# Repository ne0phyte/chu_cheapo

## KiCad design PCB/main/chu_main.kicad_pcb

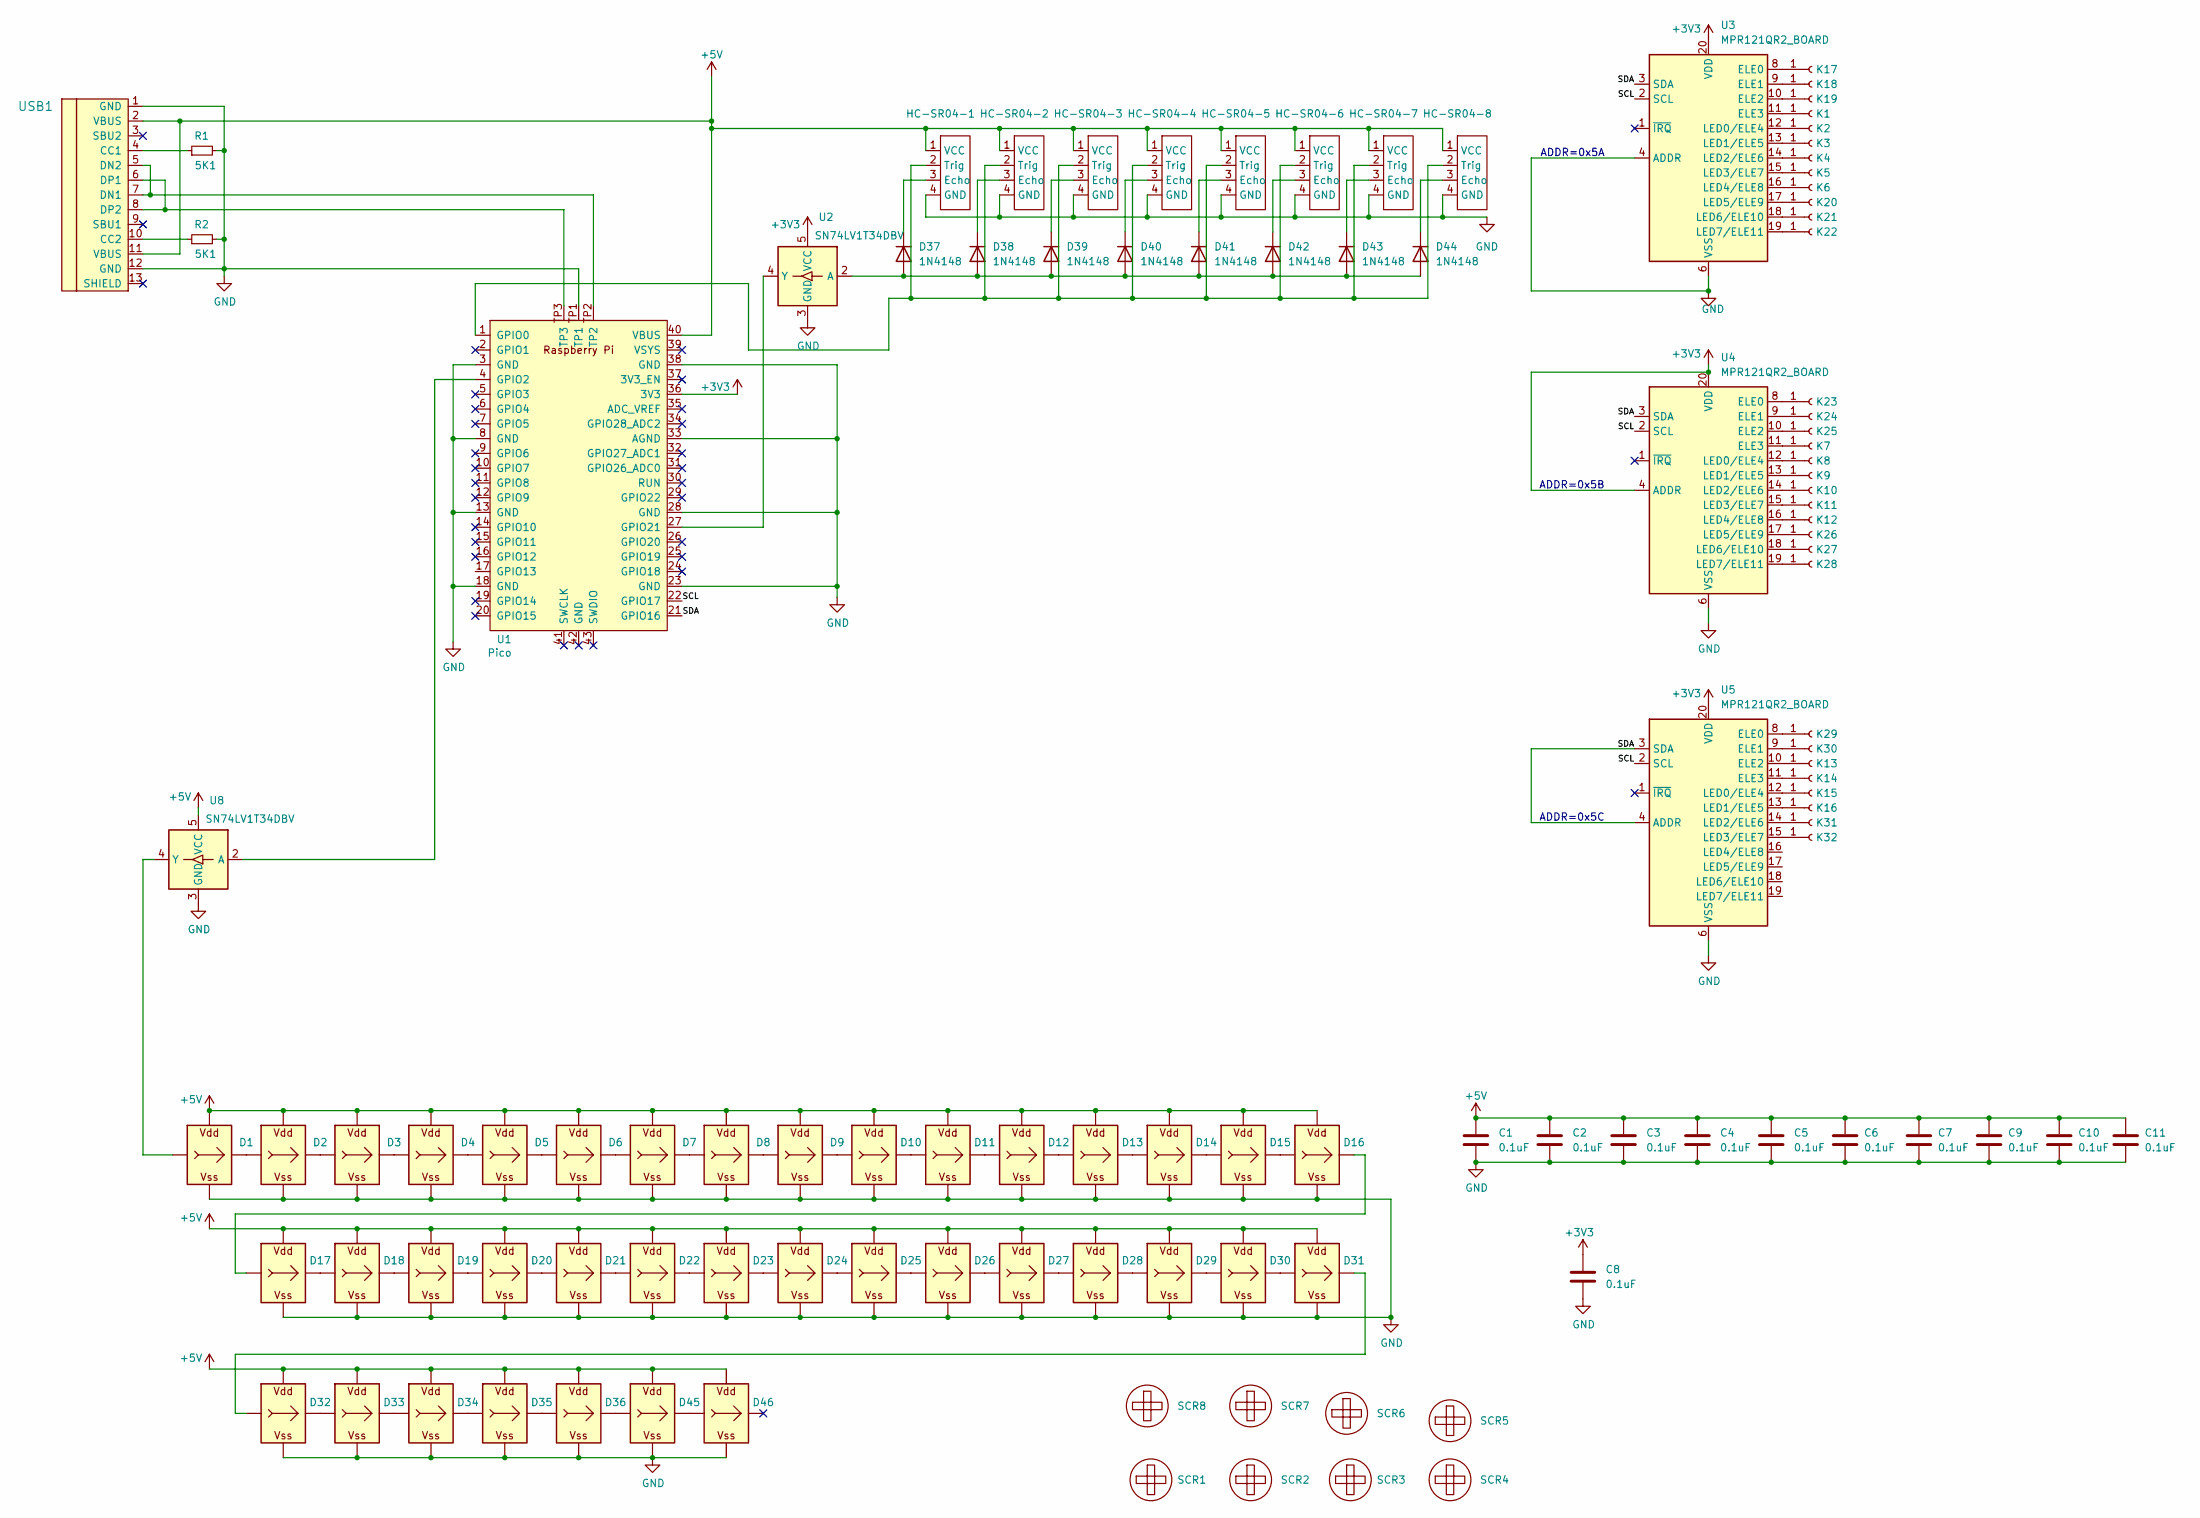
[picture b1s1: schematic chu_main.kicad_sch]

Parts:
C1, C2, C3, C4, C5, C6, C7, C8, C9, C10, C11: 0.1uF; C_0603_1608Metric_Pad1.08x0.95mm_HandSolder
D1, D2, D3, D4, D5, D6, D7, D8, D9, D10, D11, D12, D13, D14, D15, D16, D17, D18, D19, D20, D21, D22, D23, D24, D25, D26, D27, D28, D29, D30, D31, D32, D33, D34, D35, D36, D45, D46: WS2812B_Unified; WS2812D-F5
D37, D38, D39, D40, D41, D42, D43, D44: 1N4148; D_DO-35_SOD27_P7.62mm_Horizontal
HC-SR04-1, HC-SR04-2, HC-SR04-3, HC-SR04-4, HC-SR04-5, HC-SR04-6, HC-SR04-7, HC-SR04-8: HC-SR04
K1, K2, K3, K4, K5, K6, K7, K8, K9, K10, K11, K12, K13, K14, K15, K16, K17, K18, K19, K20, K21, K22, K23, K24, K25, K26, K27, K28, K29, K30, K31, K32: Conn_01x01_Female; Chu_TouchKey
R1, R2: 5K1; R_0603_1608Metric; LCSC C23186
SCR1, SCR2, SCR3, SCR4, SCR5, SCR6, SCR7, SCR8: ScrewHole; MountingHole_3.2mm_M3
U1: Pico; RPi_Pico_SMD_Pins_Strip
U2, U8: SN74LV1T34DBV; SOT-23-5_Jumper
U3, U4, U5: MPR121QR2_BOARD; MPR121_BOARD
USB1: U262-161N-4BVC11; HRO-TYPE-C-31-M-12-Assembly; LCSC C319148

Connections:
+3V3: C8.1, U1.36 (3V3), U2.5 (VCC), U3.20 (VDD), U4.4 (ADDR), U4.20 (VDD), U5.20 (VDD)
+5V: C1.1, C2.1, C3.1, C4.1, C5.1, C6.1, C7.1, C9.1, C10.1, C11.1, D1.V (VDD), D2.V (VDD), D3.V (VDD), D4.V (VDD), D5.V (VDD), D6.V (VDD), D7.V (VDD), D8.V (VDD), D9.V (VDD), D10.V (VDD), D11.V (VDD), D12.V (VDD), D13.V (VDD), D14.V (VDD), D15.V (VDD), D16.V (VDD), D17.V (VDD), D18.V (VDD), D19.V (VDD), D20.V (VDD), D21.V (VDD), D22.V (VDD), D23.V (VDD), D24.V (VDD), D25.V (VDD), D26.V (VDD), D27.V (VDD), D28.V (VDD), D29.V (VDD), D30.V (VDD), D31.V (VDD), D32.V (VDD), D33.V (VDD), D34.V (VDD), D35.V (VDD), D36.V (VDD), D45.V (VDD), D46.V (VDD), HC-SR04-1.1 (VCC), HC-SR04-2.1 (VCC), HC-SR04-3.1 (VCC), HC-SR04-4.1 (VCC), HC-SR04-5.1 (VCC), HC-SR04-6.1 (VCC), HC-SR04-7.1 (VCC), HC-SR04-8.1 (VCC), U1.40 (VBUS), U8.5 (VCC), USB1.2 (VBUS), USB1.11 (VBUS)
/SCL: U1.22 (GPIO17), U3.2 (SCL), U4.2 (SCL), U5.2 (SCL)
/SDA: U1.21 (GPIO16), U3.3 (SDA), U4.3 (SDA), U5.3 (SDA), U5.4 (ADDR)
GND: C1.2, C2.2, C3.2, C4.2, C5.2, C6.2, C7.2, C8.2, C9.2, C10.2, C11.2, D1.G (VSS), D2.G (VSS), D3.G (VSS), D4.G (VSS), D5.G (VSS), D6.G (VSS), D7.G (VSS), D8.G (VSS), D9.G (VSS), D10.G (VSS), D11.G (VSS), D12.G (VSS), D13.G (VSS), D14.G (VSS), D15.G (VSS), D16.G (VSS), D17.G (VSS), D18.G (VSS), D19.G (VSS), D20.G (VSS), D21.G (VSS), D22.G (VSS), D23.G (VSS), D24.G (VSS), D25.G (VSS), D26.G (VSS), D27.G (VSS), D28.G (VSS), D29.G (VSS), D30.G (VSS), D31.G (VSS), D32.G (VSS), D33.G (VSS), D34.G (VSS), D35.G (VSS), D36.G (VSS), D45.G (VSS), D46.G (VSS), HC-SR04-1.4 (GND), HC-SR04-2.4 (GND), HC-SR04-3.4 (GND), HC-SR04-4.4 (GND), HC-SR04-5.4 (GND), HC-SR04-6.4 (GND), HC-SR04-7.4 (GND), HC-SR04-8.4 (GND), R1.2, R2.2, U1.3 (GND), U1.8 (GND), U1.13 (GND), U1.18 (GND), U1.23 (GND), U1.28 (GND), U1.33 (AGND), U1.38 (GND), U1.TP1, U2.3 (GND), U3.4 (ADDR), U3.6 (VSS), U4.6 (VSS), U5.6 (VSS), U8.3 (GND), USB1.1 (GND), USB1.12 (GND)
unnamed: D1.I (In), U8.4 (Y)
unnamed: D1.O (Out), D2.I (In)
unnamed: D2.O (Out), D3.I (In)
unnamed: D3.O (Out), D4.I (In)
unnamed: D4.O (Out), D5.I (In)
unnamed: D5.O (Out), D6.I (In)
unnamed: D6.O (Out), D7.I (In)
unnamed: D7.O (Out), D8.I (In)
unnamed: D8.O (Out), D9.I (In)
unnamed: D9.O (Out), D10.I (In)
unnamed: D10.O (Out), D11.I (In)
unnamed: D11.O (Out), D12.I (In)
unnamed: D12.O (Out), D13.I (In)
unnamed: D13.O (Out), D14.I (In)
unnamed: D14.O (Out), D15.I (In)
unnamed: D15.O (Out), D16.I (In)
unnamed: D16.O (Out), D17.I (In)
unnamed: D17.O (Out), D18.I (In)
unnamed: D18.O (Out), D19.I (In)
unnamed: D19.O (Out), D20.I (In)
unnamed: D20.O (Out), D21.I (In)
unnamed: D21.O (Out), D22.I (In)
unnamed: D22.O (Out), D23.I (In)
unnamed: D23.O (Out), D24.I (In)
unnamed: D24.O (Out), D25.I (In)
unnamed: D25.O (Out), D26.I (In)
unnamed: D26.O (Out), D27.I (In)
unnamed: D27.O (Out), D28.I (In)
unnamed: D28.O (Out), D29.I (In)
unnamed: D29.O (Out), D30.I (In)
unnamed: D30.O (Out), D31.I (In)
unnamed: D31.O (Out), D32.I (In)
unnamed: D32.O (Out), D33.I (In)
unnamed: D33.O (Out), D34.I (In)
unnamed: D34.O (Out), D35.I (In)
unnamed: D35.O (Out), D36.I (In)
unnamed: D36.O (Out), D45.I (In)
unnamed: D37.2 (A), D38.2 (A), D39.2 (A), D40.2 (A), D41.2 (A), D42.2 (A), D43.2 (A), D44.2 (A), U2.2 (A)
unnamed: D37.1 (K), HC-SR04-1.3 (Echo)
unnamed: D38.1 (K), HC-SR04-2.3 (Echo)
unnamed: D39.1 (K), HC-SR04-3.3 (Echo)
unnamed: D40.1 (K), HC-SR04-4.3 (Echo)
unnamed: D41.1 (K), HC-SR04-5.3 (Echo)
unnamed: D42.1 (K), HC-SR04-6.3 (Echo)
unnamed: D43.1 (K), HC-SR04-7.3 (Echo)
unnamed: D44.1 (K), HC-SR04-8.3 (Echo)
unnamed: D45.O (Out), D46.I (In)
unnamed: HC-SR04-1.2 (Trig), HC-SR04-2.2 (Trig), HC-SR04-3.2 (Trig), HC-SR04-4.2 (Trig), HC-SR04-5.2 (Trig), HC-SR04-6.2 (Trig), HC-SR04-7.2 (Trig), HC-SR04-8.2 (Trig), U1.1 (GPIO0)
unnamed: K1.1, U3.11 (ELE3)
unnamed: K2.1, U3.12 (LED0/ELE4)
unnamed: K3.1, U3.13 (LED1/ELE5)
unnamed: K4.1, U3.14 (LED2/ELE6)
unnamed: K5.1, U3.15 (LED3/ELE7)
unnamed: K6.1, U3.16 (LED4/ELE8)
unnamed: K7.1, U4.11 (ELE3)
unnamed: K8.1, U4.12 (LED0/ELE4)
unnamed: K9.1, U4.13 (LED1/ELE5)
unnamed: K10.1, U4.14 (LED2/ELE6)
unnamed: K11.1, U4.15 (LED3/ELE7)
unnamed: K12.1, U4.16 (LED4/ELE8)
unnamed: K13.1, U5.10 (ELE2)
unnamed: K14.1, U5.11 (ELE3)
unnamed: K15.1, U5.12 (LED0/ELE4)
unnamed: K16.1, U5.13 (LED1/ELE5)
unnamed: K17.1, U3.8 (ELE0)
unnamed: K18.1, U3.9 (ELE1)
unnamed: K19.1, U3.10 (ELE2)
unnamed: K20.1, U3.17 (LED5/ELE9)
unnamed: K21.1, U3.18 (LED6/ELE10)
unnamed: K22.1, U3.19 (LED7/ELE11)
unnamed: K23.1, U4.8 (ELE0)
unnamed: K24.1, U4.9 (ELE1)
unnamed: K25.1, U4.10 (ELE2)
unnamed: K26.1, U4.17 (LED5/ELE9)
unnamed: K27.1, U4.18 (LED6/ELE10)
unnamed: K28.1, U4.19 (LED7/ELE11)
unnamed: K29.1, U5.8 (ELE0)
unnamed: K30.1, U5.9 (ELE1)
unnamed: K31.1, U5.14 (LED2/ELE6)
unnamed: K32.1, U5.15 (LED3/ELE7)
unnamed: U1.4 (GPIO2), U8.2 (A)
unnamed: U1.27 (GPIO21), U2.4 (Y)
unnamed: R1.1, USB1.4 (CC1)
unnamed: R2.1, USB1.10 (CC2)
unnamed: U1.TP2, USB1.5 (DN2), USB1.7 (DN1)
unnamed: U1.TP3, USB1.6 (DP1), USB1.8 (DP2)

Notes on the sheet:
ADDR=0x5C
ADDR=0x5A
ADDR=0x5B

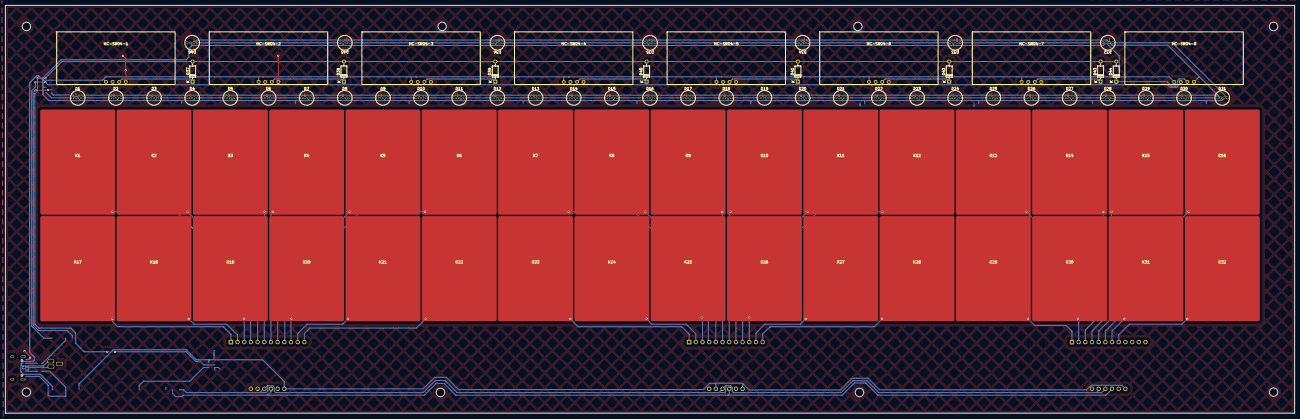
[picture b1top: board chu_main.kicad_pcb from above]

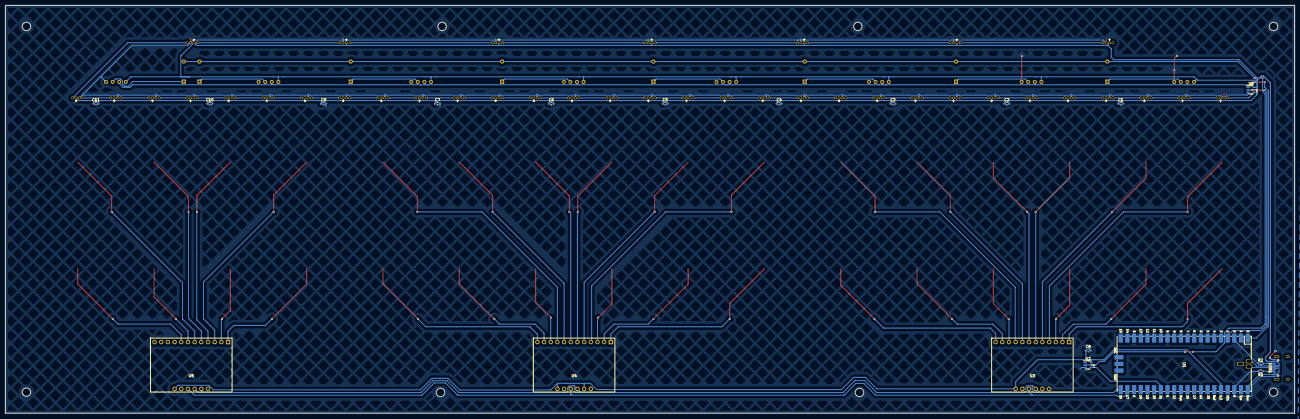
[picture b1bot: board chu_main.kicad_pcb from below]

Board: 2 copper layers, 490.0 x 155.0 mm, 114 parts (20 on the bottom side), 91 nets.

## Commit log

2024-06-12 wip full size pcb with hc-sr04 ultrasonic sensors
2024-06-12 add full size pcb
2024-06-21 Remove aime, update pins, fix slider code
